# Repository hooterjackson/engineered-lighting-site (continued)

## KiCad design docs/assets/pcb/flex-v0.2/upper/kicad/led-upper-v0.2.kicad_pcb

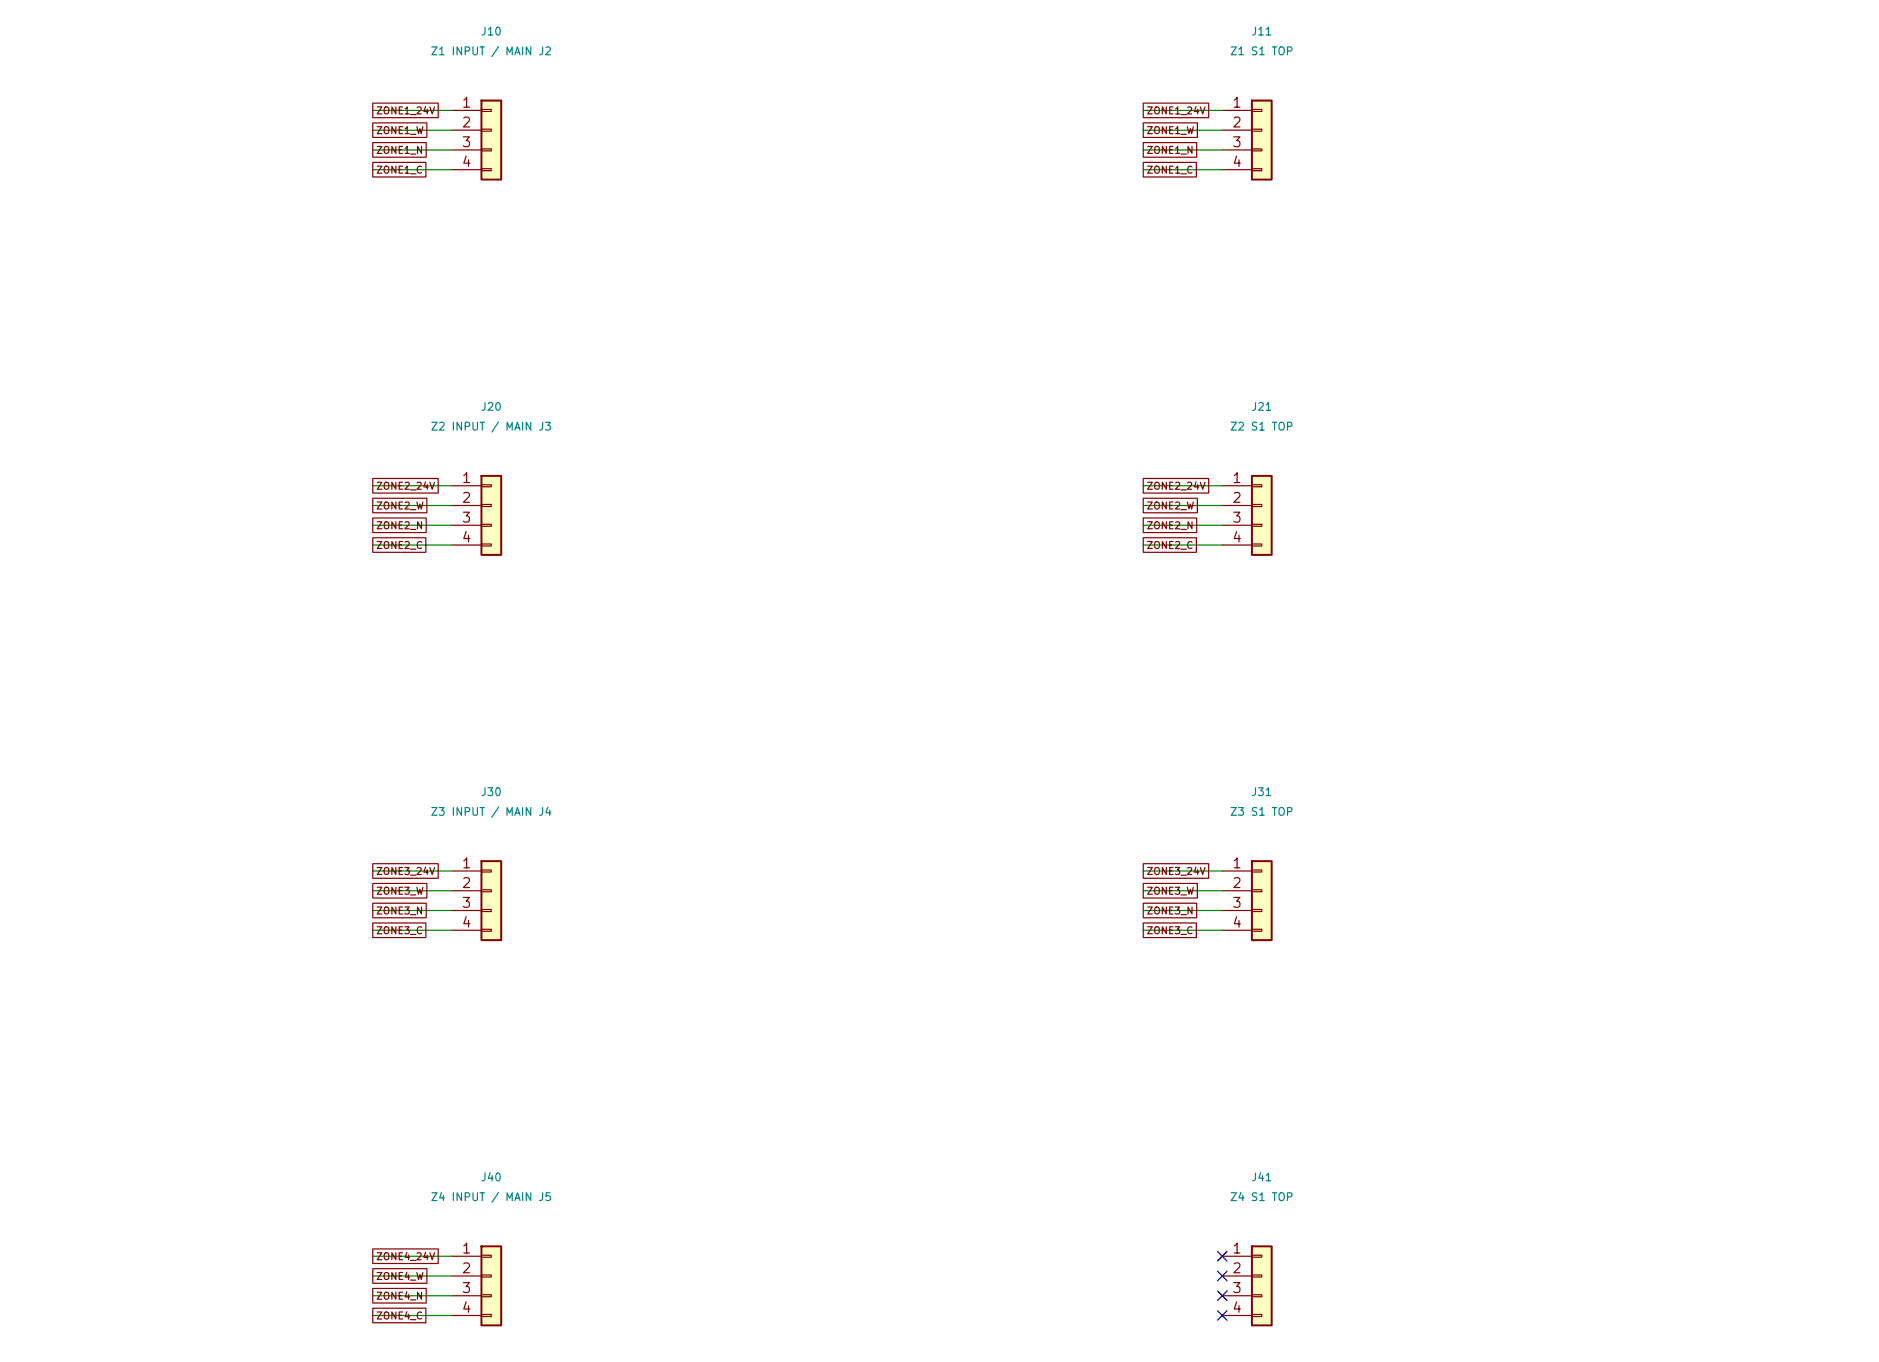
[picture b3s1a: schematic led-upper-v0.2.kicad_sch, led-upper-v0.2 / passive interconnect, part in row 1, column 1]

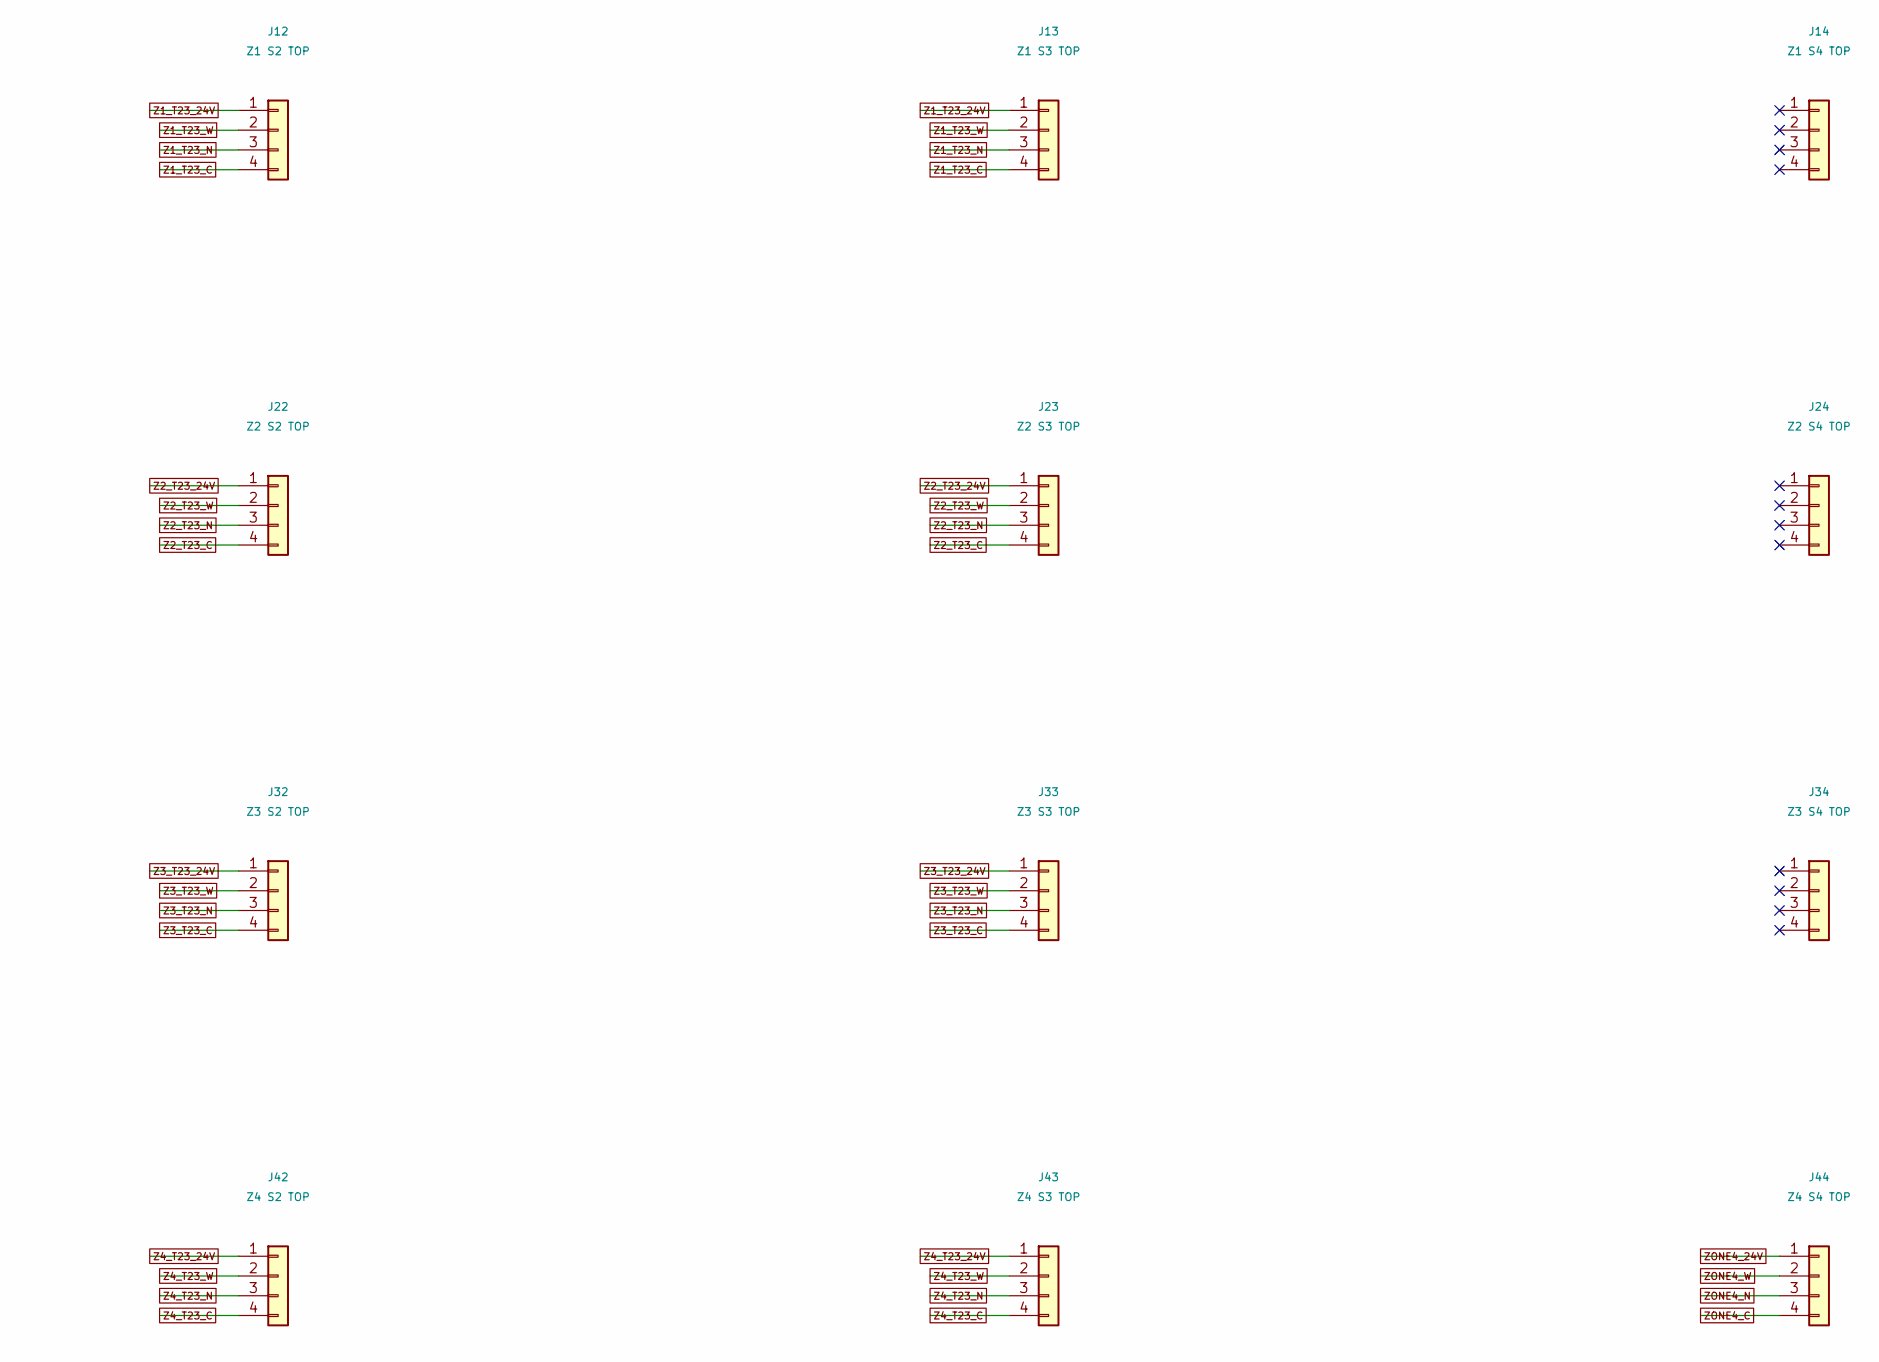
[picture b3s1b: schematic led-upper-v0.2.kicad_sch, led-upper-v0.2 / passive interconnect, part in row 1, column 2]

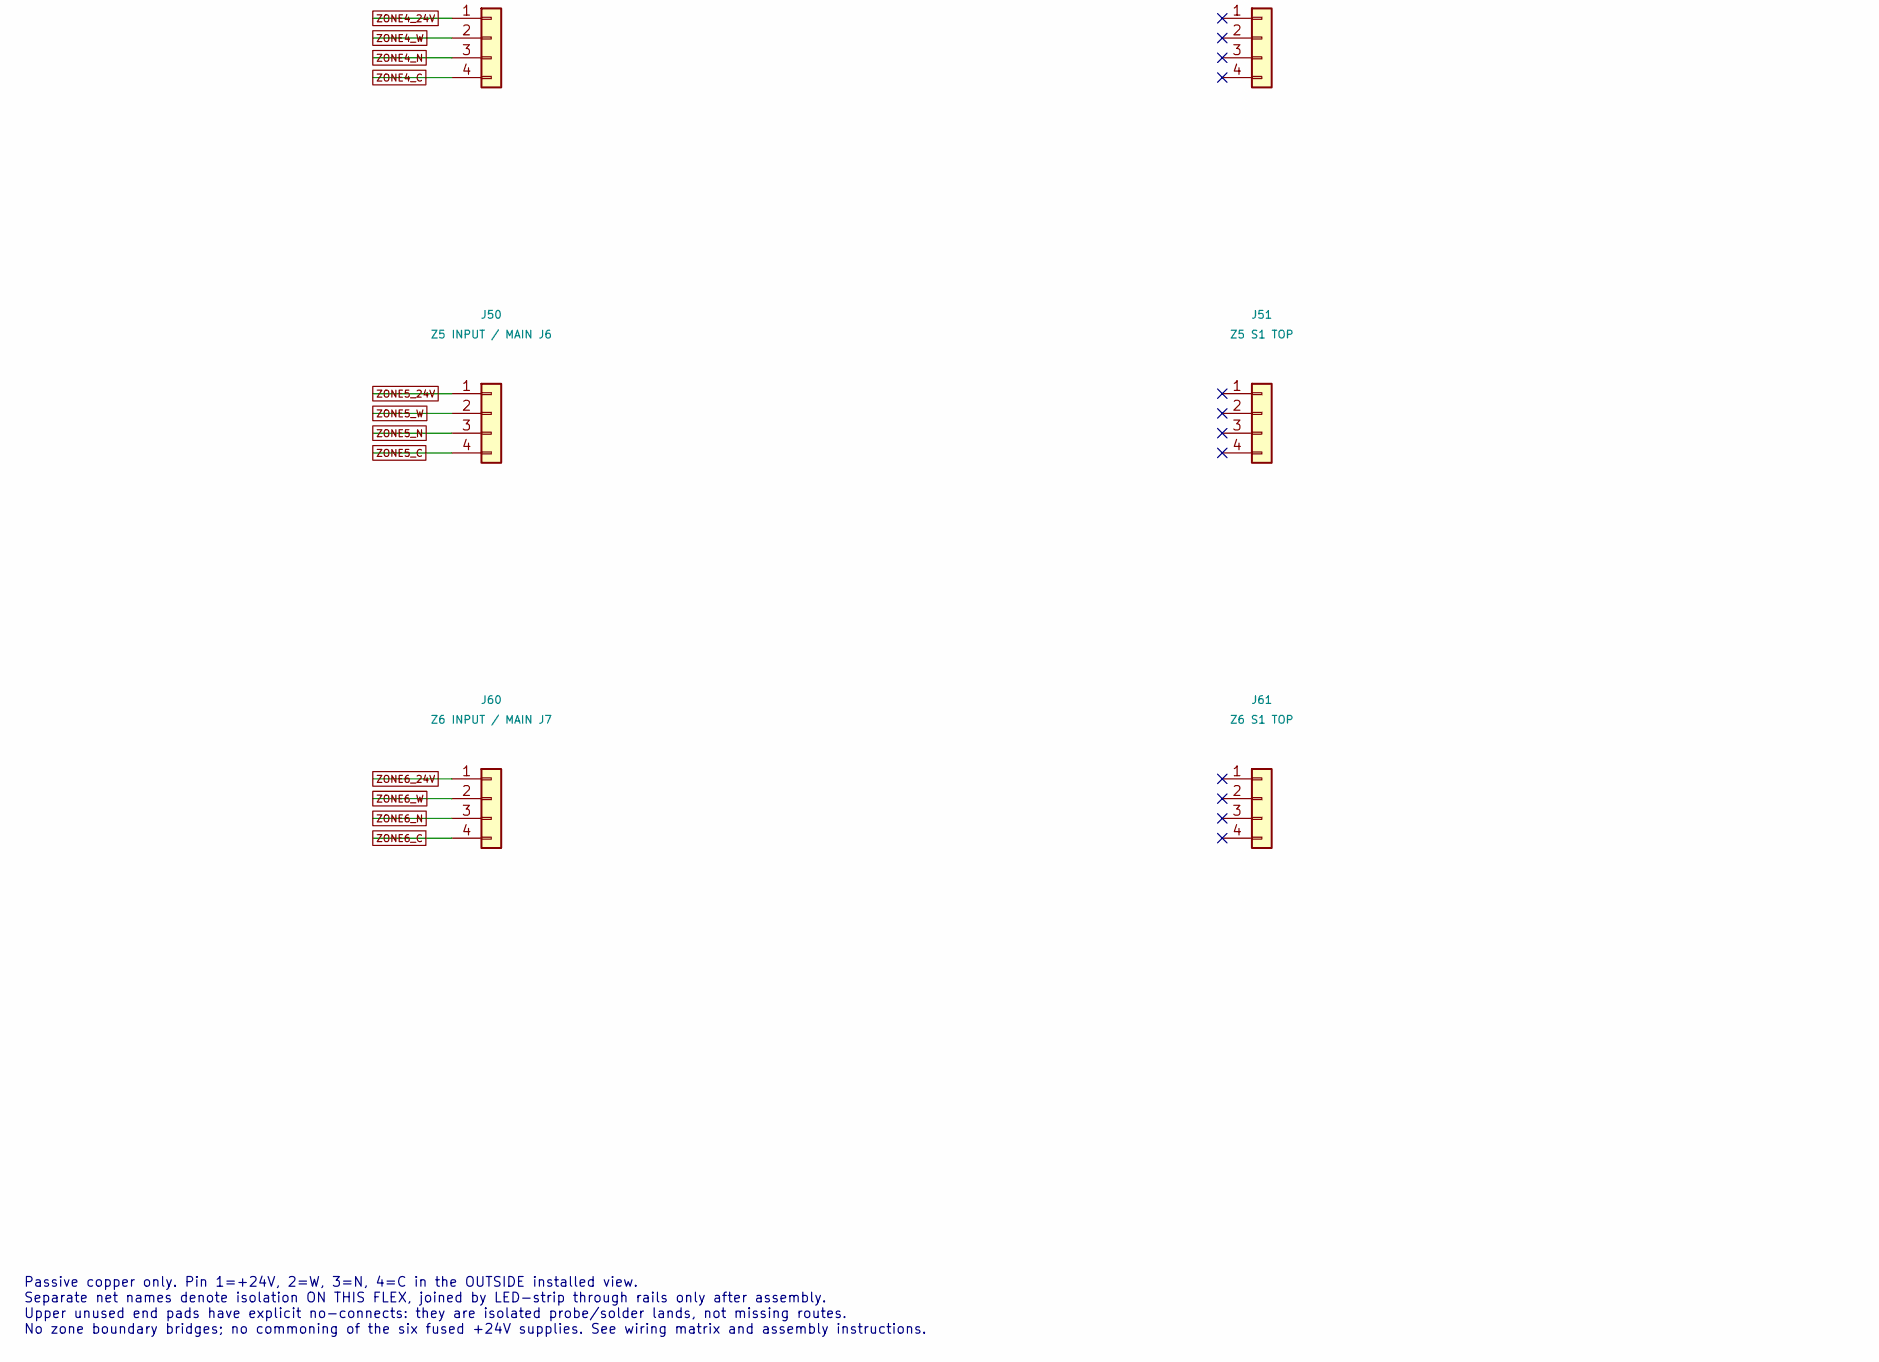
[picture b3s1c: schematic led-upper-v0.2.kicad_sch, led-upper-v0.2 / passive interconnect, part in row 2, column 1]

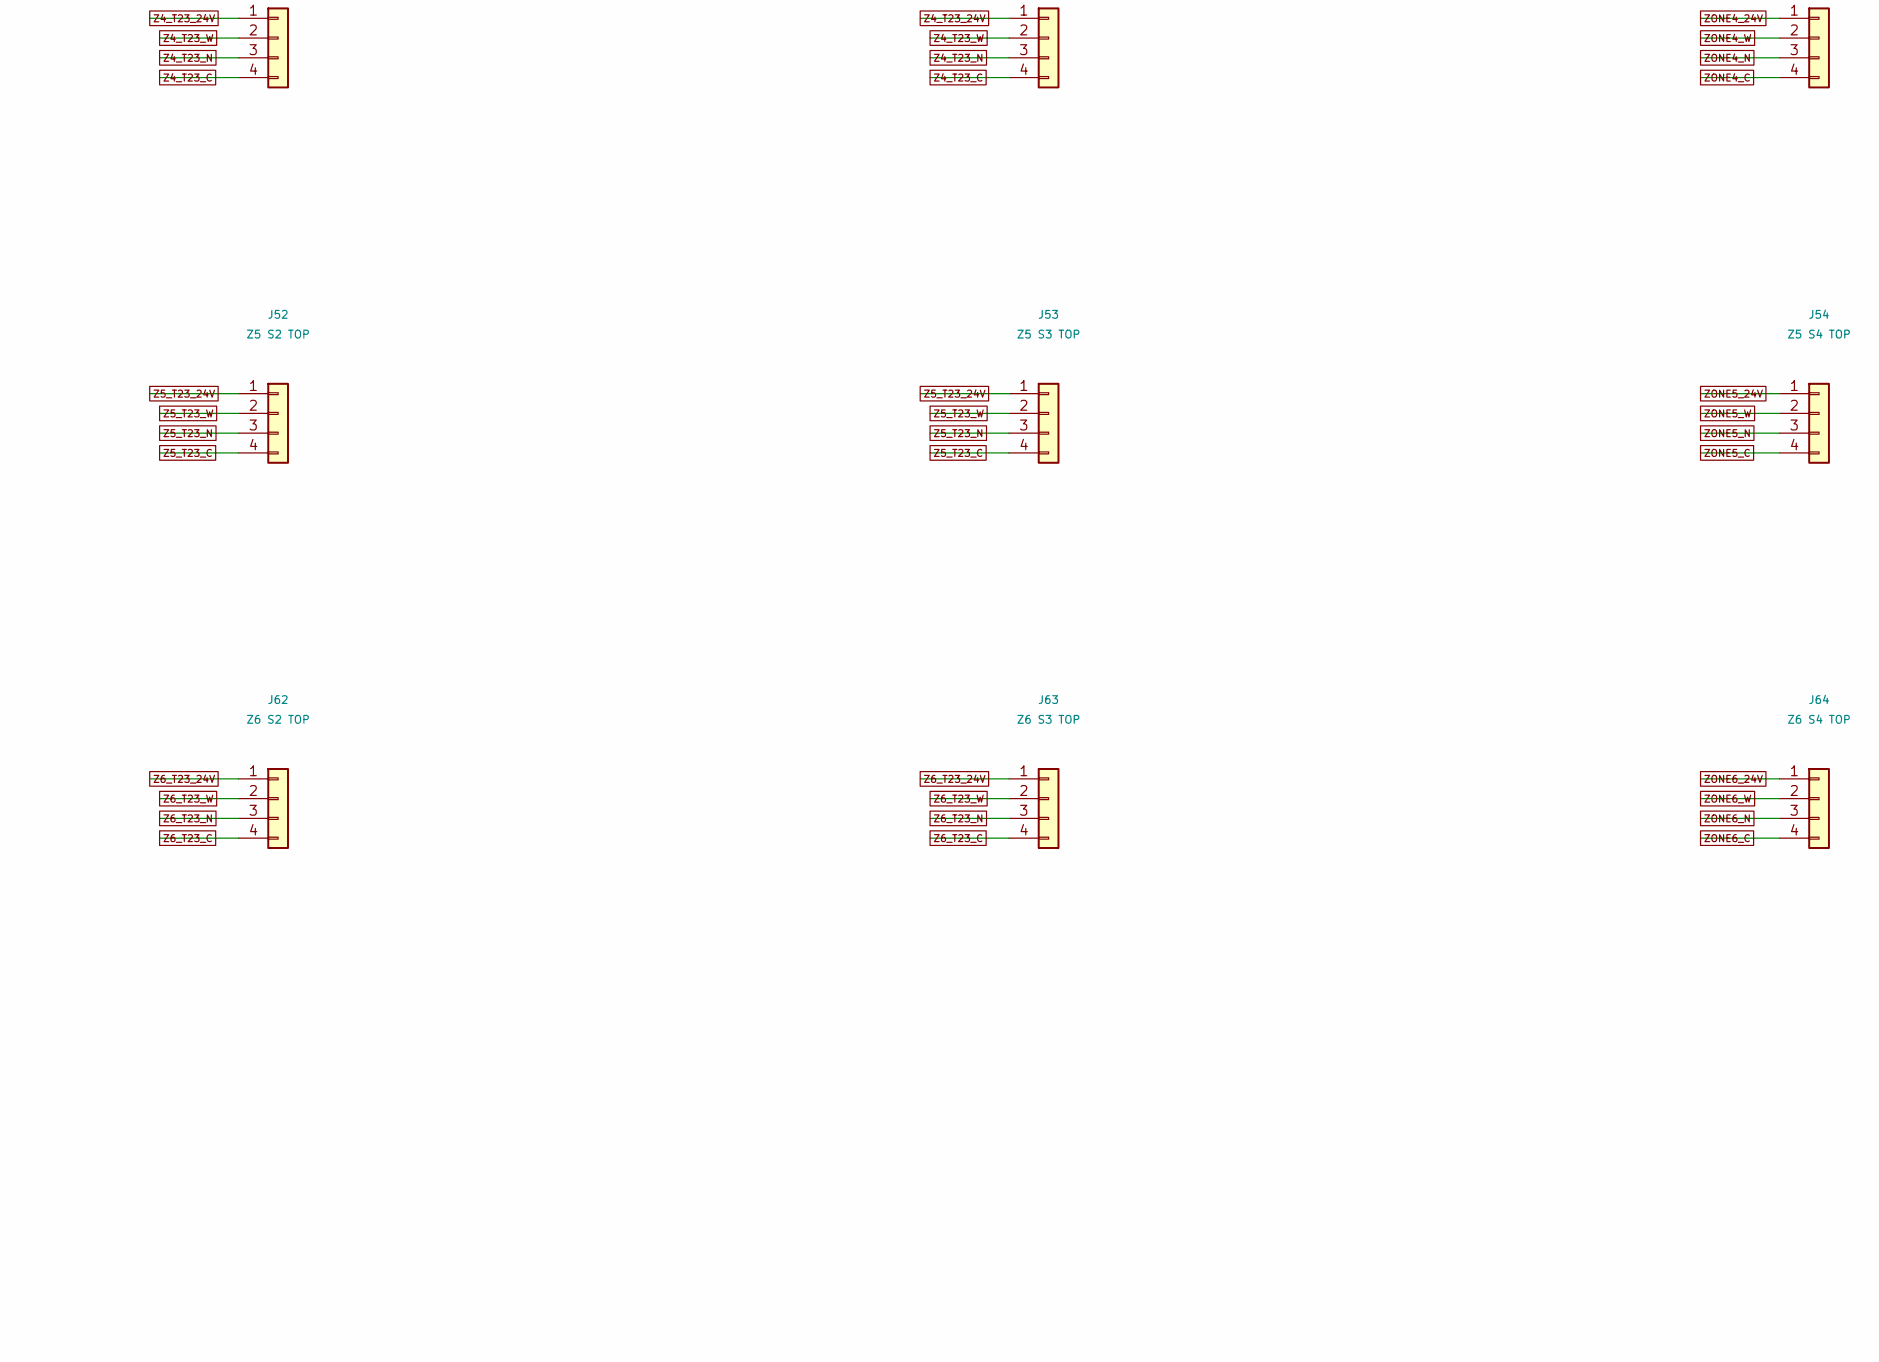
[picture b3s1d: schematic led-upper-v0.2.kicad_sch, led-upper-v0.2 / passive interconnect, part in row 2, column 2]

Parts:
J10: Z1 INPUT / MAIN J2; J10_Solder4
J11: Z1 S1 TOP; J11_Solder4
J12: Z1 S2 TOP; J12_Solder4
J13: Z1 S3 TOP; J13_Solder4
J14: Z1 S4 TOP; J14_Solder4
J20: Z2 INPUT / MAIN J3; J20_Solder4
J21: Z2 S1 TOP; J21_Solder4
J22: Z2 S2 TOP; J22_Solder4
J23: Z2 S3 TOP; J23_Solder4
J24: Z2 S4 TOP; J24_Solder4
J30: Z3 INPUT / MAIN J4; J30_Solder4
J31: Z3 S1 TOP; J31_Solder4
J32: Z3 S2 TOP; J32_Solder4
J33: Z3 S3 TOP; J33_Solder4
J34: Z3 S4 TOP; J34_Solder4
J40: Z4 INPUT / MAIN J5; J40_Solder4
J41: Z4 S1 TOP; J41_Solder4
J42: Z4 S2 TOP; J42_Solder4
J43: Z4 S3 TOP; J43_Solder4
J44: Z4 S4 TOP; J44_Solder4
J50: Z5 INPUT / MAIN J6; J50_Solder4
J51: Z5 S1 TOP; J51_Solder4
J52: Z5 S2 TOP; J52_Solder4
J53: Z5 S3 TOP; J53_Solder4
J54: Z5 S4 TOP; J54_Solder4
J60: Z6 INPUT / MAIN J7; J60_Solder4
J61: Z6 S1 TOP; J61_Solder4
J62: Z6 S2 TOP; J62_Solder4
J63: Z6 S3 TOP; J63_Solder4
J64: Z6 S4 TOP; J64_Solder4

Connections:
Z1_T23_24V: J12.1, J13.1
Z1_T23_C: J12.4, J13.4
Z1_T23_N: J12.3, J13.3
Z1_T23_W: J12.2, J13.2
Z2_T23_24V: J22.1, J23.1
Z2_T23_C: J22.4, J23.4
Z2_T23_N: J22.3, J23.3
Z2_T23_W: J22.2, J23.2
Z3_T23_24V: J32.1, J33.1
Z3_T23_C: J32.4, J33.4
Z3_T23_N: J32.3, J33.3
Z3_T23_W: J32.2, J33.2
Z4_T23_24V: J42.1, J43.1
Z4_T23_C: J42.4, J43.4
Z4_T23_N: J42.3, J43.3
Z4_T23_W: J42.2, J43.2
Z5_T23_24V: J52.1, J53.1
Z5_T23_C: J52.4, J53.4
Z5_T23_N: J52.3, J53.3
Z5_T23_W: J52.2, J53.2
Z6_T23_24V: J62.1, J63.1
Z6_T23_C: J62.4, J63.4
Z6_T23_N: J62.3, J63.3
Z6_T23_W: J62.2, J63.2
ZONE1_24V: J10.1, J11.1
ZONE1_C: J10.4, J11.4
ZONE1_N: J10.3, J11.3
ZONE1_W: J10.2, J11.2
ZONE2_24V: J20.1, J21.1
ZONE2_C: J20.4, J21.4
ZONE2_N: J20.3, J21.3
ZONE2_W: J20.2, J21.2
ZONE3_24V: J30.1, J31.1
ZONE3_C: J30.4, J31.4
ZONE3_N: J30.3, J31.3
ZONE3_W: J30.2, J31.2
ZONE4_24V: J40.1, J44.1
ZONE4_C: J40.4, J44.4
ZONE4_N: J40.3, J44.3
ZONE4_W: J40.2, J44.2
ZONE5_24V: J50.1, J54.1
ZONE5_C: J50.4, J54.4
ZONE5_N: J50.3, J54.3
ZONE5_W: J50.2, J54.2
ZONE6_24V: J60.1, J64.1
ZONE6_C: J60.4, J64.4
ZONE6_N: J60.3, J64.3
ZONE6_W: J60.2, J64.2

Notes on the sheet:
Passive copper only. Pin 1=+24V, 2=W, 3=N, 4=C in the OUTSIDE installed view. Separate net names denote isolation ON THIS FLEX, joined by LED-strip through rails only after assembly. Upper unused end pads have explicit no-connects: they are isolated probe/solder lands, not missing routes. No zone b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

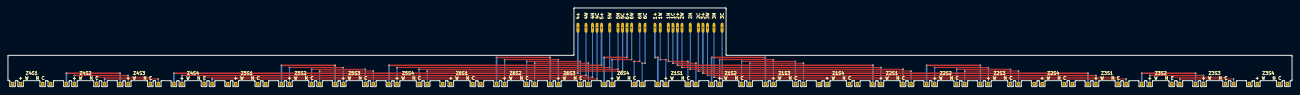
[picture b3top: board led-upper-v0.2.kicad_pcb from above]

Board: 2 copper layers, 325.0 x 19.9 mm, 30 parts (0 on the bottom side), 48 nets.

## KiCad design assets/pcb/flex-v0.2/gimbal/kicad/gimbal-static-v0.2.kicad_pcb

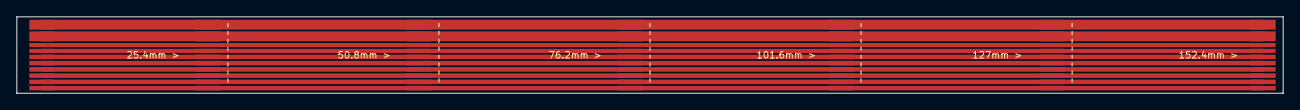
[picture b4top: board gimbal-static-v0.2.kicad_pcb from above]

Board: 2 copper layers, 152.4 x 9.2 mm, 7 parts (0 on the bottom side), 10 nets.

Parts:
J1: INPUT / KEEP THIS END; TenNet_WireBank
J2: 25.4 mm CUT TERMINATION; TenNet_WireBank
J3: 50.8 mm CUT TERMINATION; TenNet_WireBank
J4: 76.2 mm CUT TERMINATION; TenNet_WireBank
J5: 101.6 mm CUT TERMINATION; TenNet_WireBank
J6: 127 mm CUT TERMINATION; TenNet_WireBank
J7: 152.4 mm CUT TERMINATION; TenNet_WireBank

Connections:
CAN_H: J1.3, J2.3, J3.3, J4.3, J5.3, J6.3, J7.3
CAN_L: J1.4, J2.4, J3.4, J4.4, J5.4, J6.4, J7.4
GND: J1.2, J2.2, J3.2, J4.2, J5.2, J6.2, J7.2
SPOT1_LED_MINUS: J1.6, J2.6, J3.6, J4.6, J5.6, J6.6, J7.6
SPOT1_LED_PLUS: J1.5, J2.5, J3.5, J4.5, J5.5, J6.5, J7.5
SPOT2_LED_MINUS: J1.8, J2.8, J3.8, J4.8, J5.8, J6.8, J7.8
SPOT2_LED_PLUS: J1.7, J2.7, J3.7, J4.7, J5.7, J6.7, J7.7
SPOT3_LED_MINUS: J1.10, J2.10, J3.10, J4.10, J5.10, J6.10, J7.10
SPOT3_LED_PLUS: J1.9, J2.9, J3.9, J4.9, J5.9, J6.9, J7.9
V24_MOTOR2: J1.1, J2.1, J3.1, J4.1, J5.1, J6.1, J7.1

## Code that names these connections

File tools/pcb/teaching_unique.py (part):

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            "The brain and the radio. It runs the fixture's firmware, talks to both PWM expanders and the "
            "temperature sensor over I2C_SDA and I2C_SCL, drives the three spotlight requests SPOT1_PWM, "
            "SPOT2_PWM and SPOT3_PWM, speaks CAN to the motors through CAN_TX and CAN_RX, and raises "
            "LIGHT_ENABLE when it wants light. Its reset pin MCU_EN is held by R1 and C1 and can be pulled "
            "down by S1 or by the supervisor through R42."
        ),
        "how": (
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                     "lighting-enable request and GPIO1 reads whether USB is present.",
             "basis": "engineering-history/firmware_port_map.md"},
            {"kind": "documented", "evidence": INTENT,
             "text": "Module pad numbers are not GPIO numbers. Pad 25 is U0TXD (GPIO16) on net UART_TX and pad 24 "
                     "is U0RXD (GPIO17) on net UART_RX.",
             "basis": "hardware-current/hardware/rev-a/EL.kicad_sym symbol pin names"},
            {"kind": "documented", "evidence": CAD,
             "text": "The module's antenna area is kept clear of copper on all eight layers, and its body "
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        "related": ["U19", "U18", "U6", "U13", "J17", "R5", "R4", "U7", "U8", "U9"],
        "claims": [
            {"kind": "documented", "evidence": INTENT,
             "text": "Only pin 11 changed in the supply-fall correction, from LIGHT_ENABLE_SAFE to "
                     "LIGHT_REQUEST_ARMED, so the arming decision happens before the supervisor qualifies it.",
             "basis": "engineering-history/rev_a_inhibit_correction.md"},
            {"kind": "documented", "evidence": INTENT,
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        ),
        "how": (
            "An inverter outputs the opposite of its input. It is needed because the enable signal is asserted "
            "high while the expanders' control pin is asserted low. Pairing it with R6, which holds PCA_OE high "
            "by default, means the ambient outputs are disabled unless something actively enables them."
        ),
        "related": ["U2", "U3", "R6", "U19", "C5"],
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        "name": "Gate-bias load switch",
        "circuit": "gating",
        "here": (
            "Supplies GATE_BIAS, the rail that feeds all 21 ambient gate pull-ups, from +3V3. Its enable pin is "
            "LIGHT_ENABLE_SAFE, so when the board is not safe to light the gate pull-ups have no supply at all "
            "and no ambient channel can be switched on, whatever the expanders do."
        ),
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        "circuit": "input",
        "here": (
            "The board's real protection. It takes VIN24_RPP, controls the reverse-blocking transistor through "
            "EFUSE_BGATE and EFUSE_DRV, and produces the protected bus V24_BUS on pins 17 and 18. Its "
            "behaviour is programmed by the resistors around it: R500 sets the current limit, R501/R502 the "
            "undervoltage lockout, R503/R504 the overvoltage cutoff, R505/R506 the power-good threshold, and "
            "C503 the output ramp rate."
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        "circuit": "spot_supply",
        "here": (
            "Gates the spotlight rail. It takes V24_BUS and produces V24_SPOT for the three drivers, but only "
            "while LIGHT_ENABLE_SAFE is asserted on its shutdown pin -- so the spotlights lose their supply "
            "entirely, not just their control signal, when the board is not safe to light."
        ),
        "how": (
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        "name": "CAN bus transient clamp",
        "circuit": "can",
        "here": (
            "A protection array across CAN_H and CAN_L to ground, guarding the transceiver's bus pins "
            "where the harness leaves the board through the two motor connectors. Bus wiring runs "
            "outside the enclosure alongside motor power, so it is the most exposed pair on the board."
        ),
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        "name": "BOOT button",
        "circuit": "mcu",
        "here": (
            "Pulls BOOT_GPIO9 to ground. Held down while the board is reset, it makes the module start in its "
            "built-in download mode instead of running the firmware in flash."
        ),
        "how": (
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
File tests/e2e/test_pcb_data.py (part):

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        for pin, net in comps[dev]["pins"].items():
            if net and net.startswith("PWM_"):
                expander_pin[net] = (dev, int(pin))
    assert expander_pin["PWM_18"] == ("U3", 20), "the PWM 18 remap is wrong"
    assert expander_pin["PWM_20"] == ("U3", 19), "the PWM 20 remap is wrong"

    for n in range(1, 22):
        net = "PWM_%02d" % n
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        group = teach["components"]["Q1%02d" % n]["group"]
        assert group["zone"] == zone and group["channel"] == n

    assert comps["U1"]["pins"]["25"] == "UART_TX"
    assert comps["U1"]["pins"]["24"] == "UART_RX"
    for tp, net in TP_NETS.items():
        assert comps[tp]["value"] == net, tp

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    comps = {c["ref"]: c for c in board["components"]}
    assert "J10" not in comps and "J11" not in comps
    assert comps["J9"]["mpn"] == "BM06B-GHS-TBT(LF)(SN)"
    assert comps["J9"]["pins"] == {"1":"SPOT1_LED_PLUS", "2":"SPOT1_LED_MINUS", "3":"SPOT2_LED_PLUS", "4":"SPOT2_LED_MINUS", "5":"SPOT3_LED_PLUS", "6":"SPOT3_LED_MINUS"}
    assert comps["J9"]["side"] == comps["J13"]["side"] == "B"
    assert "J12" in comps

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
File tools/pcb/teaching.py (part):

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    "C517": ("U14", "V24_BUS", "bypass at the spotlight eFuse's input"),
    "C518": ("U14", "V24_SPOT", "bypass at the spotlight eFuse's output"),
    "C30": ("J14", "USB_VBUS", "bypass on the USB bus voltage right at the connector"),
    "C31": ("U17", "USB_VBUS", "bypass on the USB bus voltage at the data mux's supply pin"),
}

# ref -> (rail, role)
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# ref -> (direction, rail, node, what it achieves)
PULLS = {
    "R1": ("up", "+3V3", "MCU_EN", "holds the module out of reset once 3.3 V is up; with C1 it sets the reset delay"),
    "R2": ("up", "+3V3", "BOOT_GPIO9", "keeps the boot strap high, so the module runs its own firmware unless S2 is held down"),
    "R3": ("up", "+3V3", "BOOT_GPIO8", "keeps the second boot strap in its normal state"),
    "R4": ("down", "GND", "LIGHT_ENABLE", "makes the firmware's lighting request default to off, including before any firmware runs"),
    "R5": ("down", "GND", "ARM", "makes the board read as disarmed whenever the ARM switch is open or unplugged"),
    "R6": ("up", "+3V3", "PCA_OE", "holds the expanders' outputs disabled by default, since output-enable is active-low"),
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    "R10": ("down", "GND", "SPOT2_PWM", "keeps spotlight 2's request off while the controller is unprogrammed or in reset"),
    "R11": ("down", "GND", "SPOT3_PWM", "keeps spotlight 3's request off while the controller is unprogrammed or in reset"),
    "R20": ("up", "+3V3", "CAN_TX", "holds the transmit line in its idle state so an unprogrammed controller cannot jam the bus"),
    "R21": ("down", "GND", "CAN_STB", "ties the transceiver's standby pin low, which selects normal mode"),
    "R36": ("up", "+3V3", "USB_PRESENT_N", "holds the USB-present signal high, meaning absent, until Q30 pulls it down"),
    "R40": ("down", "GND", "USB_VBUS", "bleeds the small USB island so it cannot hold a stale 'USB is present' state after unplugging"),
    "R507": ("down", "GND", "EFUSE_IMON", "turns the eFuse's current-monitor output into a voltage"),
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
    if ref == "J9":
        entry.update(name="Three-channel spotlight connector", circuit="spot",
            here="One six-contact plug carries all three spotlight LED pairs: " + _contacts(pins) + ". It sits beside the separate J13 tilt connection, so their wires leave toward the same arm harness.",
            how="Pins 1/2, 3/4 and 5/6 serve channels 1, 2 and 3. A shared plastic housing does not join the circuits: each LED-minus returns to its own driver inductor, never to ground or another channel.",
            related=["U7", "U8", "U9", "L502", "L503", "L504", "J13"],
            claims=[{"kind":"documented", "evidence":"cad-checked", "text":"Six independent contacts replace the three former two-contact sockets. J10 and J11 are absent.", "basis":"Current native J9 pins and schematic parity"}],
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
